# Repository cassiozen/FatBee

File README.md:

# Fat Bee 🐝

## A familiar keyboard with unfamiliar comfort

**Fat Bee** is a compact mechanical keyboard that takes a gentle, scientific approach to ergonomics without making you relearn how to type.

## What?

The keyboard layout we use today is ancient. Literally. It was designed in the 1800s to keep typewriters from jamming — not to keep your wrists from hurting.

Modern ergonomic keyboards try to fix that, but many go too far. Curved key wells, columnar layouts, and deep splits can help *if* you’re willing to adapt. Most people aren't.

**Fat Bee bridges the gap between comfort and familiarity.**
It's the kind of keyboard you can sit down at and just start using — whether you hunt and peck, type with two fingers, or mastered touch typing in high school.

## Gallery

## What's in this repo?

- 3D-print case & palm rest source
- PCB source (KiCad)
- Keyboard layout (standard keyboard-layout-editor.com JSON)
- ZMK profile (coming soon)

## FatBee's Characteristics

### 👐 Gently split layout  

Just enough angle to align your hands naturally.  
**Reduces ulnar deviation** — that awkward wrist bend that causes strain over time.

### 🏕️ 5.5° tenting

Raises the inner edge of the keyboard to match your forearm's natural rotation.  
**Avoids pronation**, keeps your forearm bones from squeezing the carpal tunnel.

### 🛏️ Built-in palm rest + low rear angle

Supports your hands without forcing your wrists to bend upward.  
**Prevents wrist extension**, a common source of fatigue.

### 🧲 Centralized alphas

Alphanumerics are dead center, not off to the left side.  
**Keeps your arms and shoulders aligned** with your body.

## The control cluster you didn’t know you needed

While redesigning the layout, something unexpected happened.

By centering the keys and adjusting row spacing, we created a weird little negative space on the left. Instead of ignoring it, we filled it with function:

- **Escape**, aligned with the numeric row
  (no layer gymnastics for `~` and `'`)
- **Fn key + 3 utility buttons**:
  - Volume up (tap), volume down (Fn+tap)  
  - Brightness up/down  
  - App switcher (like Cmd+Tab / Shift+Cmd+Tab)

## Specs

- 69 keys, number row, arrow cluster
- Low-profile Choc switches

## Inspiration

- **Apple keyboards** – Subtly decreasing row stagger (between rows R2 and R3) since forever. Probably for style. Still, it adds up - used on FatBee.  
- **[Jones layout](https://github.com/jpskenn/Jones)** – Combines centralized alphanumerics with non-staggered rows R2-R3.
- **[Logitech Wave](https://www.logitech.com/en-us/products/keyboards/wave-keys.html)** - Despite feeling mushy and cheap, it does deliver great ergonomic improvements while still looking familiar.

## License

CERN Open Hardware Licence Version 2 - Weakly Reciprocal (CERN-OHL-W V2).

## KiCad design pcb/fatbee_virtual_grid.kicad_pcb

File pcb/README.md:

The PCB is supposed to be bended to accomodate for the 3 different tenting angles. It has a cutting pattern on the middle to facilitate this, and should be manufactured with 0.6mm thickness.

# PCB characteristics:

- Kailh sockets for hot swaping
- Header pins to connect a Nice!nano or compatible microcontroller board.
- 

# Grid

To optimize the number of required pins, the PCB is wired in a virtual row/column matrix with 7 columns and 10 rows. The columns are wired in pairs, meaning each virtual column spans across two physical key columns. The left side of the PCB is exclusively wired to the odd-numbered rows, while the right side is wired exclusively to the even-numbered rows.

## Warning

Still under development, use at your own risk. I just ordered this version from JLCPCB and if it works I'll be glad to remove this warning ;)

## What's up with all those screws?

There are three constraints:

- Make it bend
- Make it sturdy enough for hotswap to work
- Make it practical, using common materials and manufacturing practices (so one can use services like PCBWay or JLCPCB...)

> "I don't know... Have you tried a thin PCB with, like, lots of screws?".
>> Brain cell on the back, hand raised, a little bit ashamed of the suggestion.

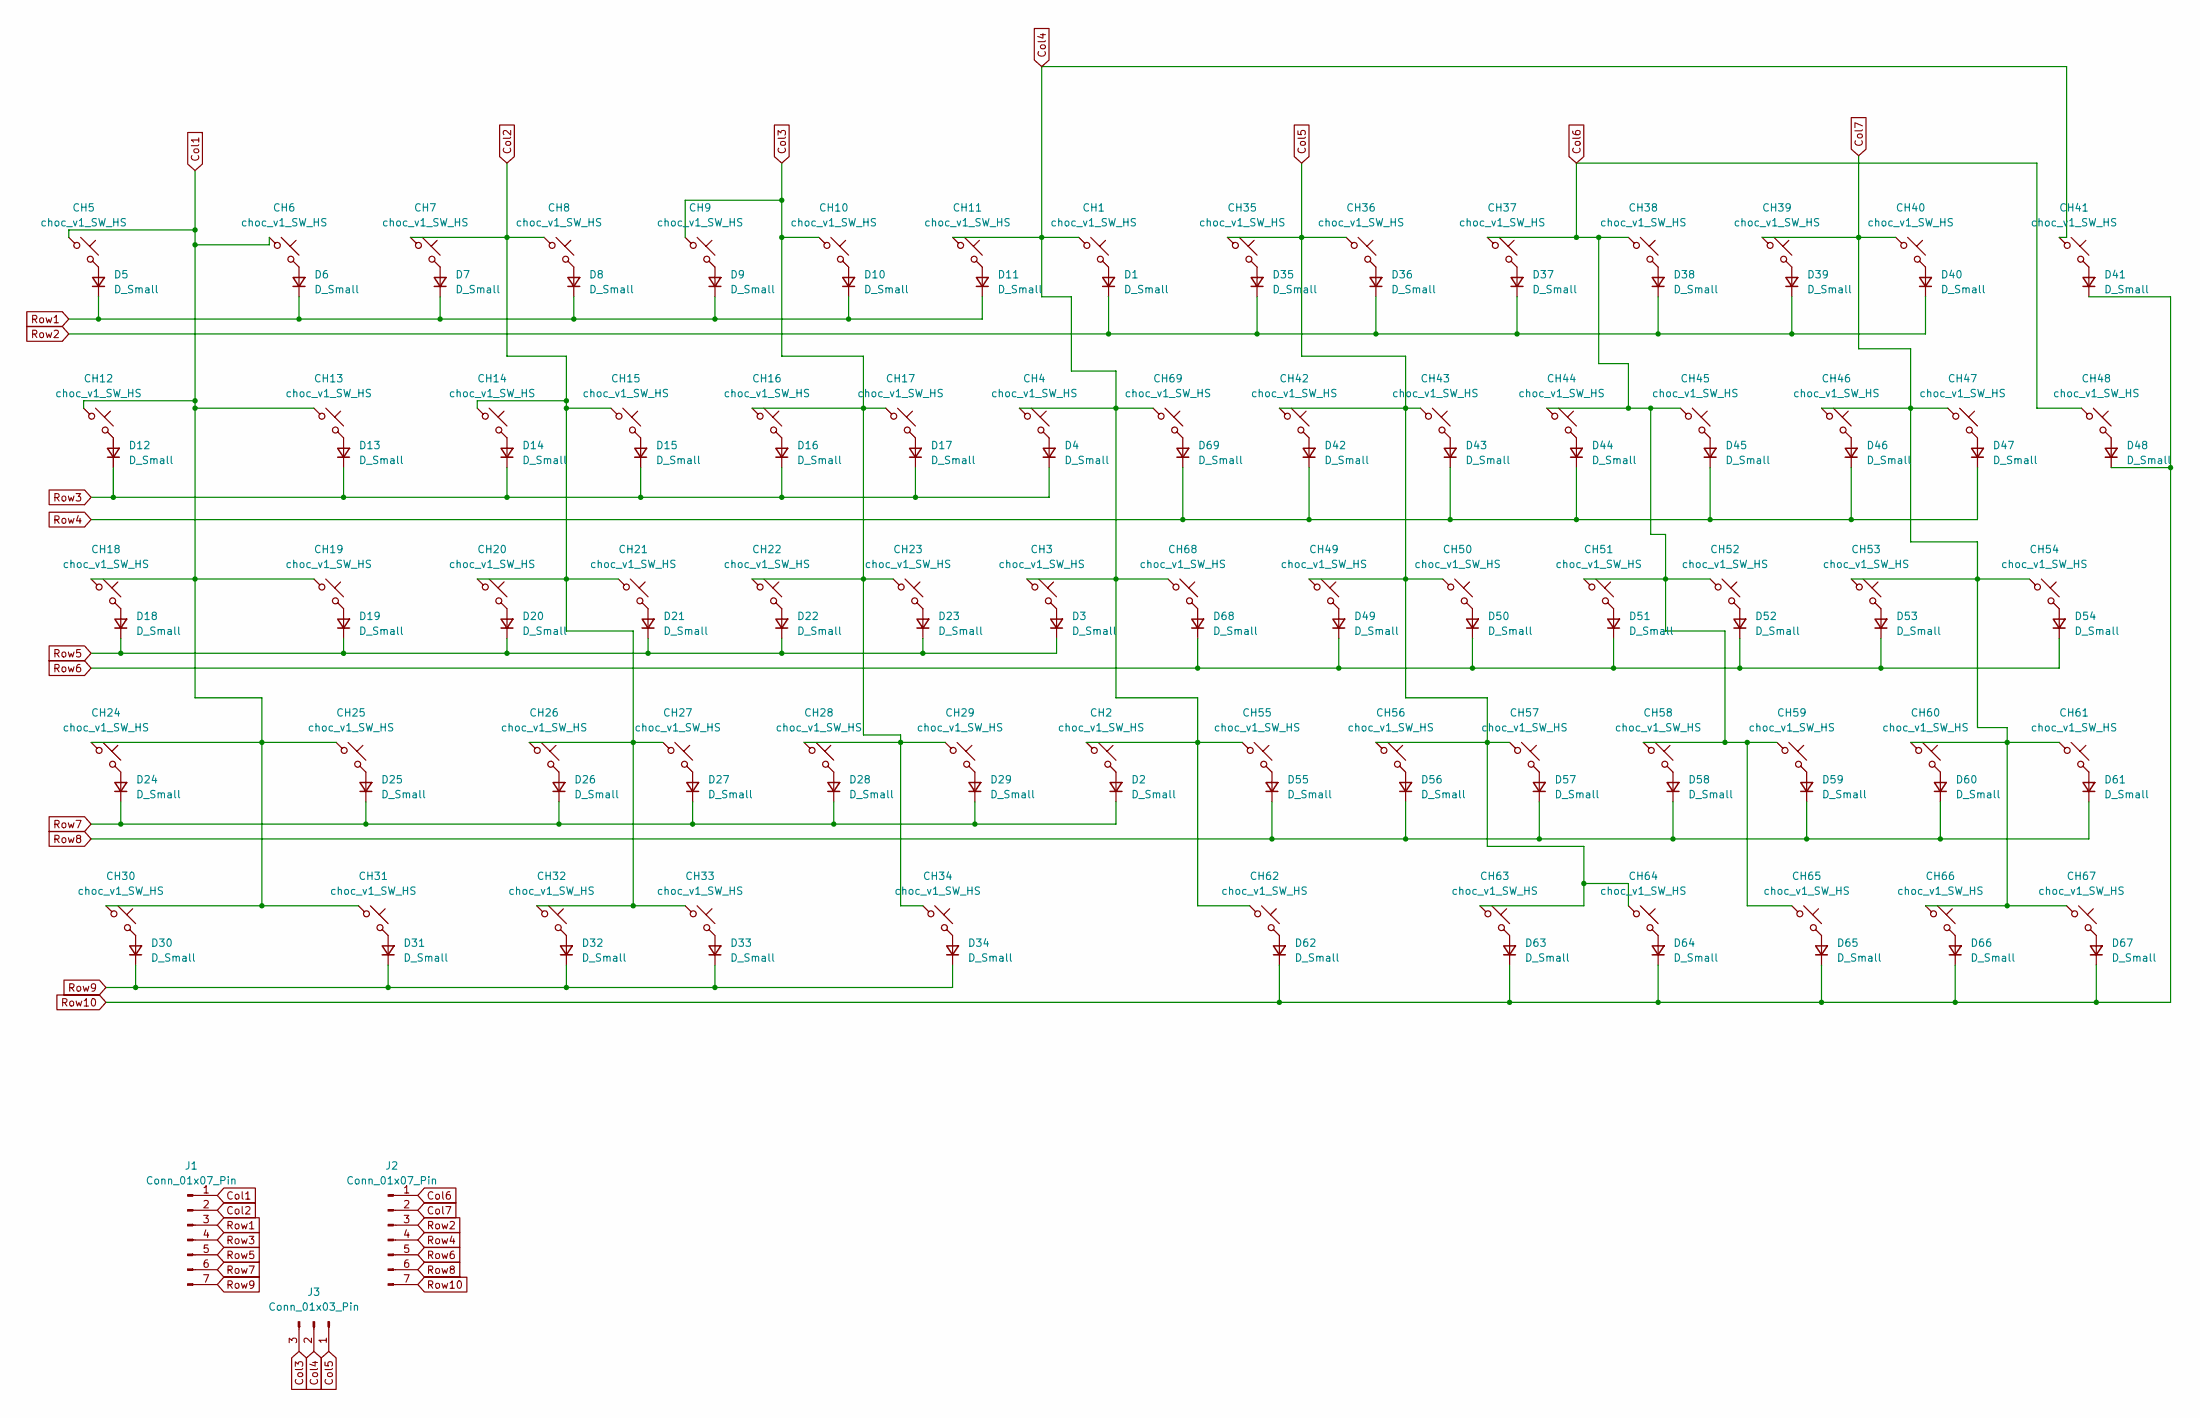
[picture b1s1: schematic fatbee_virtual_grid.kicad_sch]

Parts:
CH1, CH2, CH3, CH4, CH5, CH6, CH7, CH8, CH9, CH10, CH11, CH12, CH13, CH14, CH15, CH16, CH17, CH18, CH19, CH20, CH21, CH22, CH23, CH24, CH25, CH26, CH27, CH28, CH29, CH30, CH31, CH32, CH33, CH34, CH35, CH36, CH37, CH38, CH39, CH40, CH41, CH42, CH43, CH44, CH45, CH46, CH47, CH48, CH49, CH50, CH51, CH52, CH53, CH54, CH55, CH56, CH57, CH58, CH59, CH60, CH61, CH62, CH63, CH64, CH65, CH66, CH67, CH68, CH69: choc_v1_SW_HS; SW_choc_v1_HS_CPG135001S30_1u
D1, D2, D3, D4, D5, D6, D7, D8, D9, D10, D11, D12, D13, D14, D15, D16, D17, D18, D19, D20, D21, D22, D23, D24, D25, D26, D27, D28, D29, D30, D31, D32, D33, D34, D35, D36, D37, D38, D39, D40, D41, D42, D43, D44, D45, D46, D47, D48, D49, D50, D51, D52, D53, D54, D55, D56, D57, D58, D59, D60, D61, D62, D63, D64, D65, D66, D67, D68, D69: D_Small; D_SOD-123
J1, J2: Conn_01x07_Pin; PinHeader_1x07_P2.54mm_Vertical
J3: Conn_01x03_Pin; PinHeader_1x03_P2.54mm_Vertical

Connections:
Col1: CH5.1, CH6.1, CH12.1, CH13.1, CH18.1, CH19.1, CH24.1, CH25.1, CH30.1, CH31.1, J1.1
Col2: CH7.1, CH8.1, CH14.1, CH15.1, CH20.1, CH21.1, CH26.1, CH27.1, CH32.1, CH33.1, J1.2
Col3: CH9.1, CH10.1, CH16.1, CH17.1, CH22.1, CH23.1, CH28.1, CH29.1, CH34.1, J3.3
Col4: CH1.1, CH2.1, CH3.1, CH4.1, CH11.1, CH41.1, CH55.1, CH62.1, CH68.1, CH69.1, J3.2
Col5: CH35.1, CH36.1, CH42.1, CH43.1, CH49.1, CH50.1, CH56.1, CH57.1, CH63.1, CH64.1, J3.1
Col6: CH37.1, CH38.1, CH44.1, CH45.1, CH48.1, CH51.1, CH52.1, CH58.1, CH59.1, CH65.1, J2.1
Col7: CH39.1, CH40.1, CH46.1, CH47.1, CH53.1, CH54.1, CH60.1, CH61.1, CH66.1, CH67.1, J2.2
unnamed: CH1.2, D1.2 (A)
unnamed: CH2.2, D2.2 (A)
unnamed: CH3.2, D3.2 (A)
unnamed: CH4.2, D4.2 (A)
unnamed: CH5.2, D5.2 (A)
unnamed: CH6.2, D6.2 (A)
unnamed: CH7.2, D7.2 (A)
unnamed: CH8.2, D8.2 (A)
unnamed: CH9.2, D9.2 (A)
unnamed: CH10.2, D10.2 (A)
unnamed: CH11.2, D11.2 (A)
unnamed: CH12.2, D12.2 (A)
unnamed: CH13.2, D13.2 (A)
unnamed: CH14.2, D14.2 (A)
unnamed: CH15.2, D15.2 (A)
unnamed: CH16.2, D16.2 (A)
unnamed: CH17.2, D17.2 (A)
unnamed: CH18.2, D18.2 (A)
unnamed: CH19.2, D19.2 (A)
unnamed: CH20.2, D20.2 (A)
unnamed: CH21.2, D21.2 (A)
unnamed: CH22.2, D22.2 (A)
unnamed: CH23.2, D23.2 (A)
unnamed: CH24.2, D24.2 (A)
unnamed: CH25.2, D25.2 (A)
unnamed: CH26.2, D26.2 (A)
unnamed: CH27.2, D27.2 (A)
unnamed: CH28.2, D28.2 (A)
unnamed: CH29.2, D29.2 (A)
unnamed: CH30.2, D30.2 (A)
unnamed: CH31.2, D31.2 (A)
unnamed: CH32.2, D32.2 (A)
unnamed: CH33.2, D33.2 (A)
unnamed: CH34.2, D34.2 (A)
unnamed: CH35.2, D35.2 (A)
unnamed: CH36.2, D36.2 (A)
unnamed: CH37.2, D37.2 (A)
unnamed: CH38.2, D38.2 (A)
unnamed: CH39.2, D39.2 (A)
unnamed: CH40.2, D40.2 (A)
unnamed: CH41.2, D41.2 (A)
unnamed: CH42.2, D42.2 (A)
unnamed: CH43.2, D43.2 (A)
unnamed: CH44.2, D44.2 (A)
unnamed: CH45.2, D45.2 (A)
unnamed: CH46.2, D46.2 (A)
unnamed: CH47.2, D47.2 (A)
unnamed: CH48.2, D48.2 (A)
unnamed: CH49.2, D49.2 (A)
unnamed: CH50.2, D50.2 (A)
unnamed: CH51.2, D51.2 (A)
unnamed: CH52.2, D52.2 (A)
unnamed: CH53.2, D53.2 (A)
unnamed: CH54.2, D54.2 (A)
unnamed: CH55.2, D55.2 (A)
unnamed: CH56.2, D56.2 (A)
unnamed: CH57.2, D57.2 (A)
unnamed: CH58.2, D58.2 (A)
unnamed: CH59.2, D59.2 (A)
unnamed: CH60.2, D60.2 (A)
unnamed: CH61.2, D61.2 (A)
unnamed: CH62.2, D62.2 (A)
unnamed: CH63.2, D63.2 (A)
unnamed: CH64.2, D64.2 (A)
unnamed: CH65.2, D65.2 (A)
unnamed: CH66.2, D66.2 (A)
unnamed: CH67.2, D67.2 (A)
unnamed: CH68.2, D68.2 (A)
unnamed: CH69.2, D69.2 (A)
Row1: D5.1 (K), D6.1 (K), D7.1 (K), D8.1 (K), D9.1 (K), D10.1 (K), D11.1 (K), J1.3
Row2: D1.1 (K), D35.1 (K), D36.1 (K), D37.1 (K), D38.1 (K), D39.1 (K), D40.1 (K), J2.3
Row3: D4.1 (K), D12.1 (K), D13.1 (K), D14.1 (K), D15.1 (K), D16.1 (K), D17.1 (K), J1.4
Row4: D42.1 (K), D43.1 (K), D44.1 (K), D45.1 (K), D46.1 (K), D47.1 (K), D69.1 (K), J2.4
Row5: D3.1 (K), D18.1 (K), D19.1 (K), D20.1 (K), D21.1 (K), D22.1 (K), D23.1 (K), J1.5
Row6: D49.1 (K), D50.1 (K), D51.1 (K), D52.1 (K), D53.1 (K), D54.1 (K), D68.1 (K), J2.5
Row7: D2.1 (K), D24.1 (K), D25.1 (K), D26.1 (K), D27.1 (K), D28.1 (K), D29.1 (K), J1.6
Row8: D55.1 (K), D56.1 (K), D57.1 (K), D58.1 (K), D59.1 (K), D60.1 (K), D61.1 (K), J2.6
Row9: D30.1 (K), D31.1 (K), D32.1 (K), D33.1 (K), D34.1 (K), J1.7
Row10: D41.1 (K), D48.1 (K), D62.1 (K), D63.1 (K), D64.1 (K), D65.1 (K), D66.1 (K), D67.1 (K), J2.7

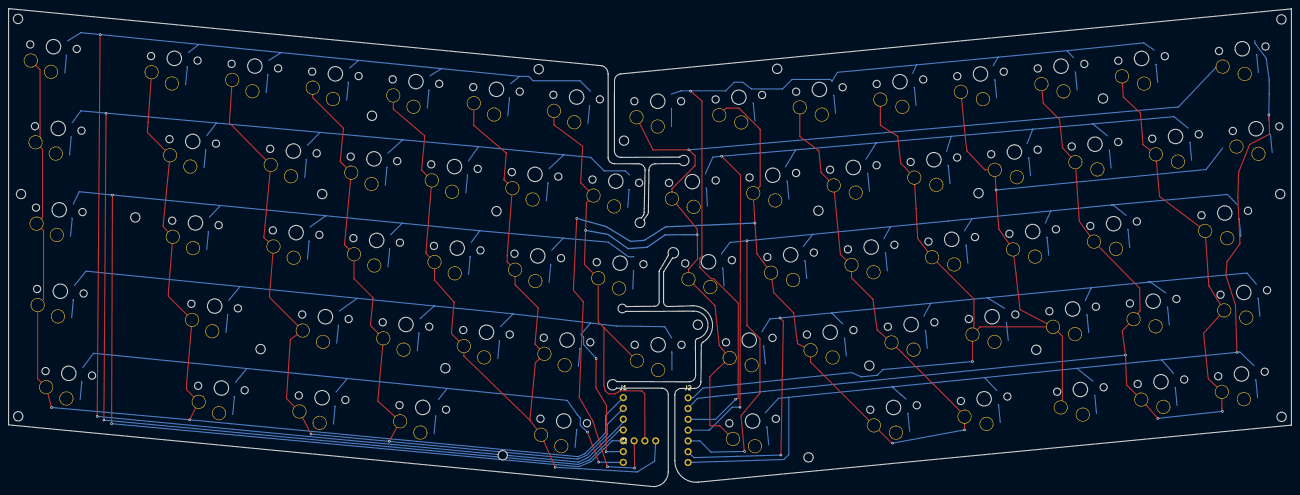
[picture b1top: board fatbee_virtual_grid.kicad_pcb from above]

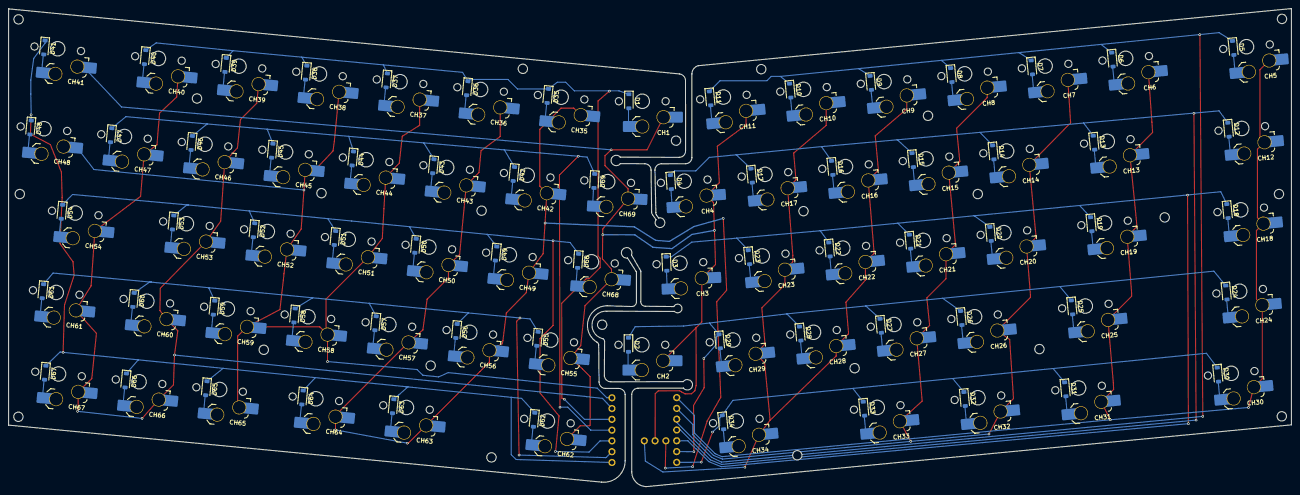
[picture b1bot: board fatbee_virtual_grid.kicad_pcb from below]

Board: 2 copper layers, 302.0 x 112.5 mm, 141 parts (138 on the bottom side), 86 nets.

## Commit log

2024-08-06 File extension
2024-08-06 Added license
2024-08-06 Content updates
2024-08-06 Typo cleanup in readme
2024-08-07 Slightly size adjustments on central keys
2024-08-07 left half PCB beta
2024-08-07 PCB Readme
2024-08-07 Updaded readme
2024-08-14 PCB maybe working?
2024-08-14 updated version
2024-08-14 Updated PCB readme
2024-08-14 Readme adjustments
2024-08-14 Added prior art
2024-08-15 License update
2024-11-20 Updated picture
2025-05-08 four thousand holes in Blackburn Lancashire
